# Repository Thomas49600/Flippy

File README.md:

# Flippy
Introducing Flippy! The all-in-one modular 3D printed electromechanical seven-segment display. Through the use of 14 electromagnets, each digit is able to quickly and mechanically display both numbers and letters. This creates a unique and satisfying display.

To build your own, check the full build instructions on Instructables: https://www.instructables.com/3D-Printed-Electromechanical-7-Segment-Display/

Or watch the YouTube video below (Link: https://youtu.be/np4NRMKOG6U)

This project falls under the CC BY-NC-SA 4.0 Licence

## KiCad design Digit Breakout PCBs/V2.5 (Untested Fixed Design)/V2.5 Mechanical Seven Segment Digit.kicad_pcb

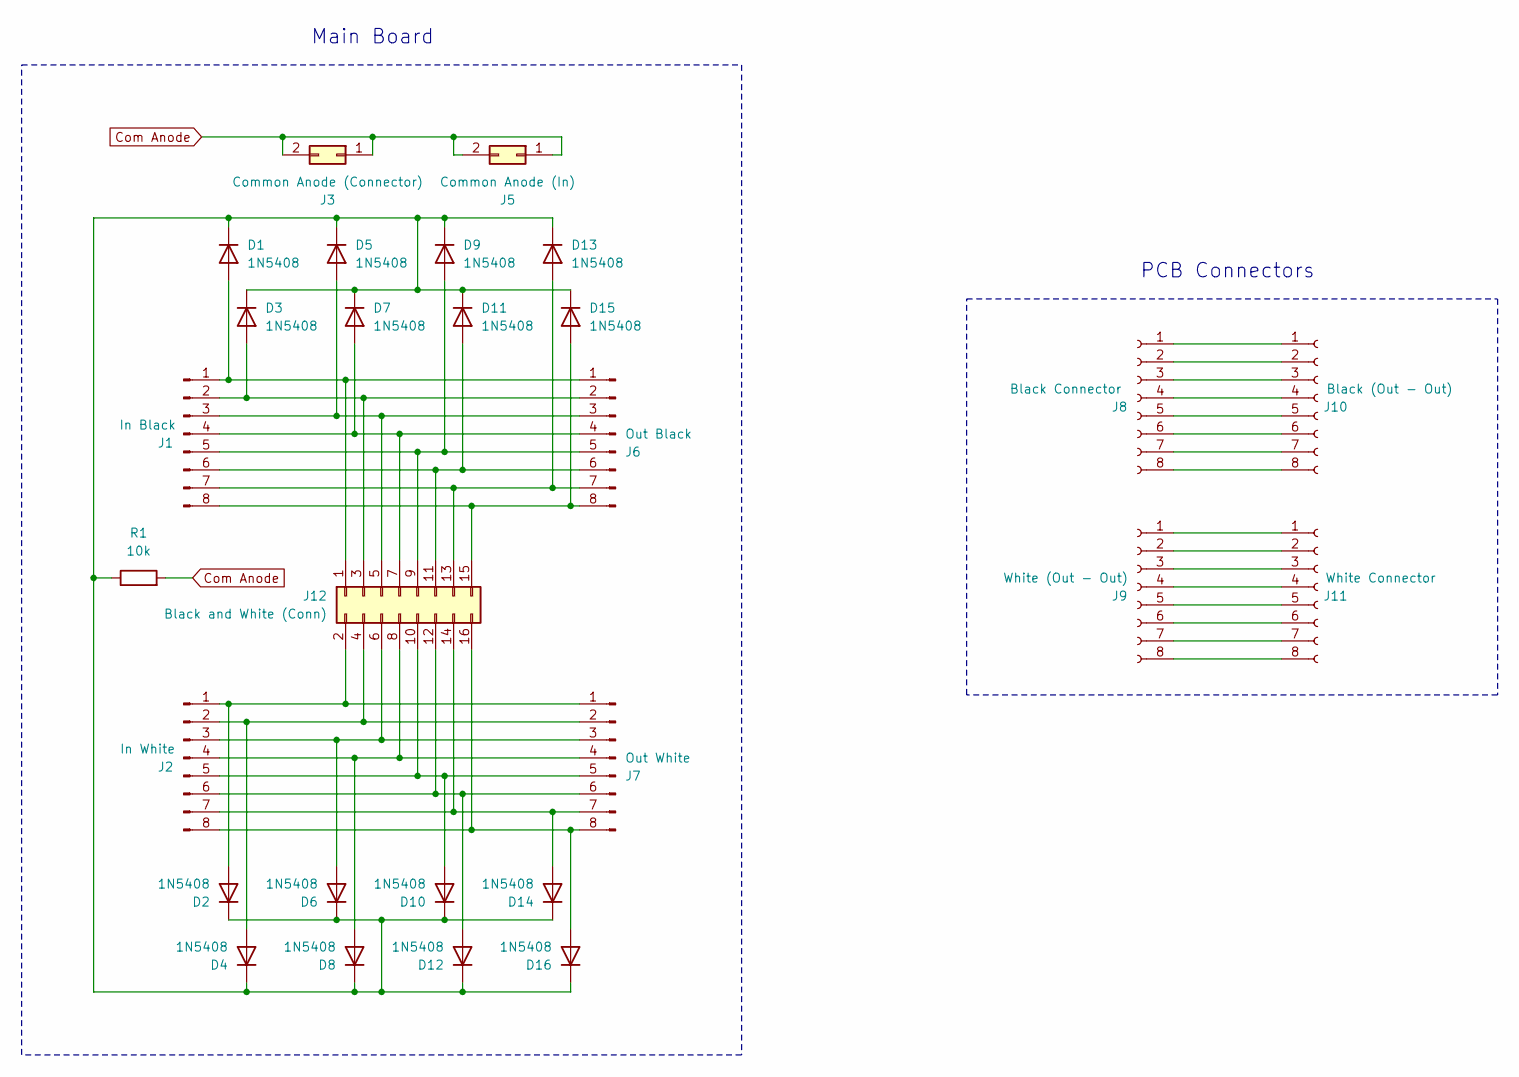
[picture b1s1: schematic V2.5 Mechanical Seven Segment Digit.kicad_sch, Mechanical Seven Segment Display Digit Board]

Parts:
D1, D2, D3, D4, D5, D6, D7, D8, D9, D10, D11, D12, D13, D14, D15, D16: 1N5408; D_DO-201AD_P15.24mm_Horizontal
J1: In Black; PinSocket_1x08_P2.54mm_Vertical
J2: In White; PinSocket_1x08_P2.54mm_Vertical
J3: Common Anode (Connector); PinSocket_2x01_P2.54mm_Vertical
J5: Common Anode (In); PinSocket_2x01_P2.54mm_Vertical
J6: Out Black; PinSocket_1x08_P2.54mm_Vertical
J7: Out White; PinSocket_1x08_P2.54mm_Vertical
J8: Black Connector; PinSocket_1x08_P2.54mm_Vertical
J9: White (Out - Out); PinSocket_1x08_P2.54mm_Vertical
J10: Black (Out - Out); PinSocket_1x08_P2.54mm_Vertical
J11: White Connector; PinSocket_1x08_P2.54mm_Vertical
J12: Black and White (Conn); PinSocket_2x08_P2.54mm_Vertical
R1: 10k; R_Axial_DIN0207_L6.3mm_D2.5mm_P7.62mm_Horizontal

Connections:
Com Anode: J3.1, J3.2, J5.1, J5.2, R1.2
unnamed: D1.2 (A), J1.1, J6.1, J12.1
unnamed: D1.1 (K), D2.1 (K), D3.1 (K), D4.1 (K), D5.1 (K), D6.1 (K), D7.1 (K), D8.1 (K), D9.1 (K), D10.1 (K), D11.1 (K), D12.1 (K), D13.1 (K), D14.1 (K), D15.1 (K), D16.1 (K), R1.1
unnamed: D2.2 (A), J2.1, J7.1, J12.2
unnamed: D3.2 (A), J1.2, J6.2, J12.3
unnamed: D4.2 (A), J2.2, J7.2, J12.4
unnamed: D5.2 (A), J1.3, J6.3, J12.5
unnamed: D6.2 (A), J2.3, J7.3, J12.6
unnamed: D7.2 (A), J1.4, J6.4, J12.7
unnamed: D8.2 (A), J2.4, J7.4, J12.8
unnamed: D9.2 (A), J1.5, J6.5, J12.9
unnamed: D10.2 (A), J2.5, J7.5, J12.10
unnamed: D11.2 (A), J1.6, J6.6, J12.11
unnamed: D12.2 (A), J2.6, J7.6, J12.12
unnamed: D13.2 (A), J1.7, J6.7, J12.13
unnamed: D14.2 (A), J2.7, J7.7, J12.14
unnamed: D15.2 (A), J1.8, J6.8, J12.15
unnamed: D16.2 (A), J2.8, J7.8, J12.16
unnamed: J8.1, J10.1
unnamed: J8.2, J10.2
unnamed: J8.3, J10.3
unnamed: J8.4, J10.4
unnamed: J8.5, J10.5
unnamed: J8.6, J10.6
unnamed: J8.7, J10.7
unnamed: J8.8, J10.8
unnamed: J9.1, J11.1
unnamed: J9.2, J11.2
unnamed: J9.3, J11.3
unnamed: J9.4, J11.4
unnamed: J9.5, J11.5
unnamed: J9.6, J11.6
unnamed: J9.7, J11.7
unnamed: J9.8, J11.8

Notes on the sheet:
Main Board
PCB Connectors

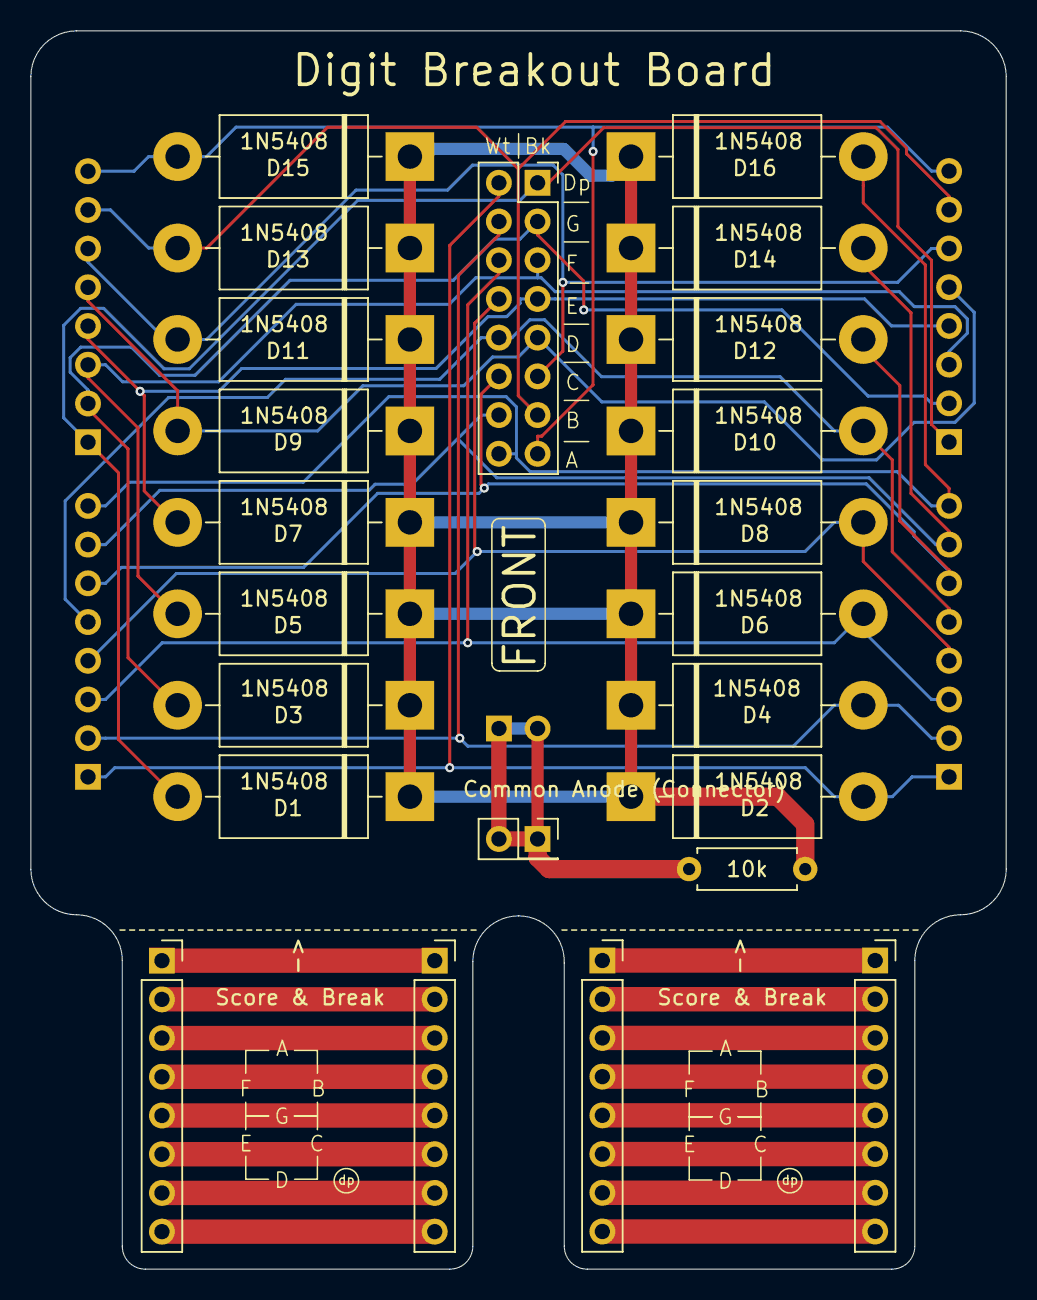
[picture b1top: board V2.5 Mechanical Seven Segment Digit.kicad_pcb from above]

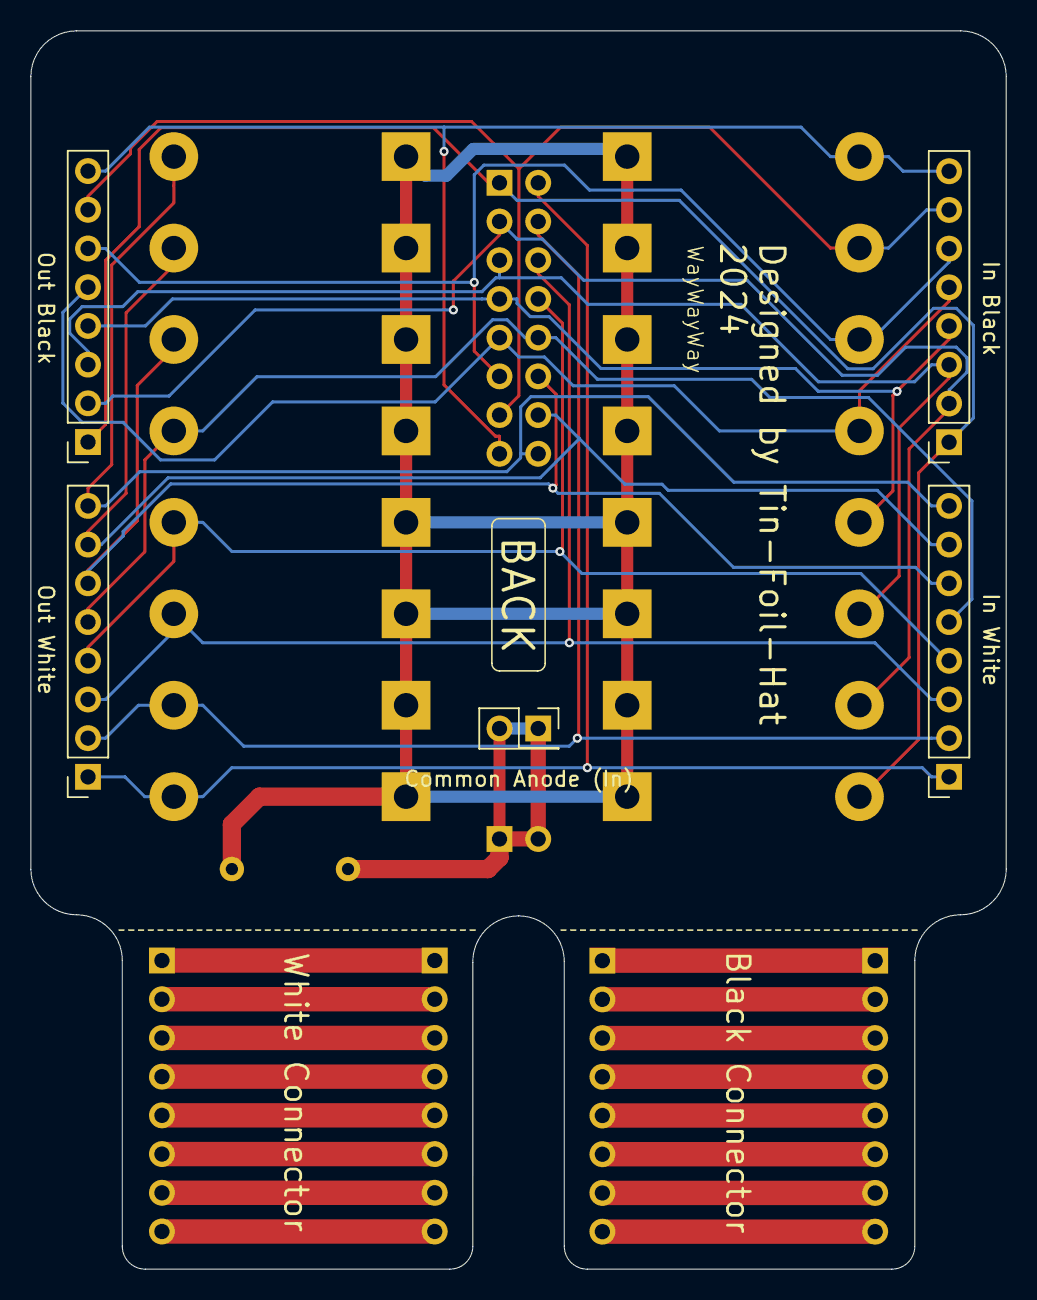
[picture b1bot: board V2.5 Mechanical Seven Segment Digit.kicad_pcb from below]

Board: 2 copper layers, 64.0 x 81.3 mm, 28 parts (5 on the bottom side), 34 nets.

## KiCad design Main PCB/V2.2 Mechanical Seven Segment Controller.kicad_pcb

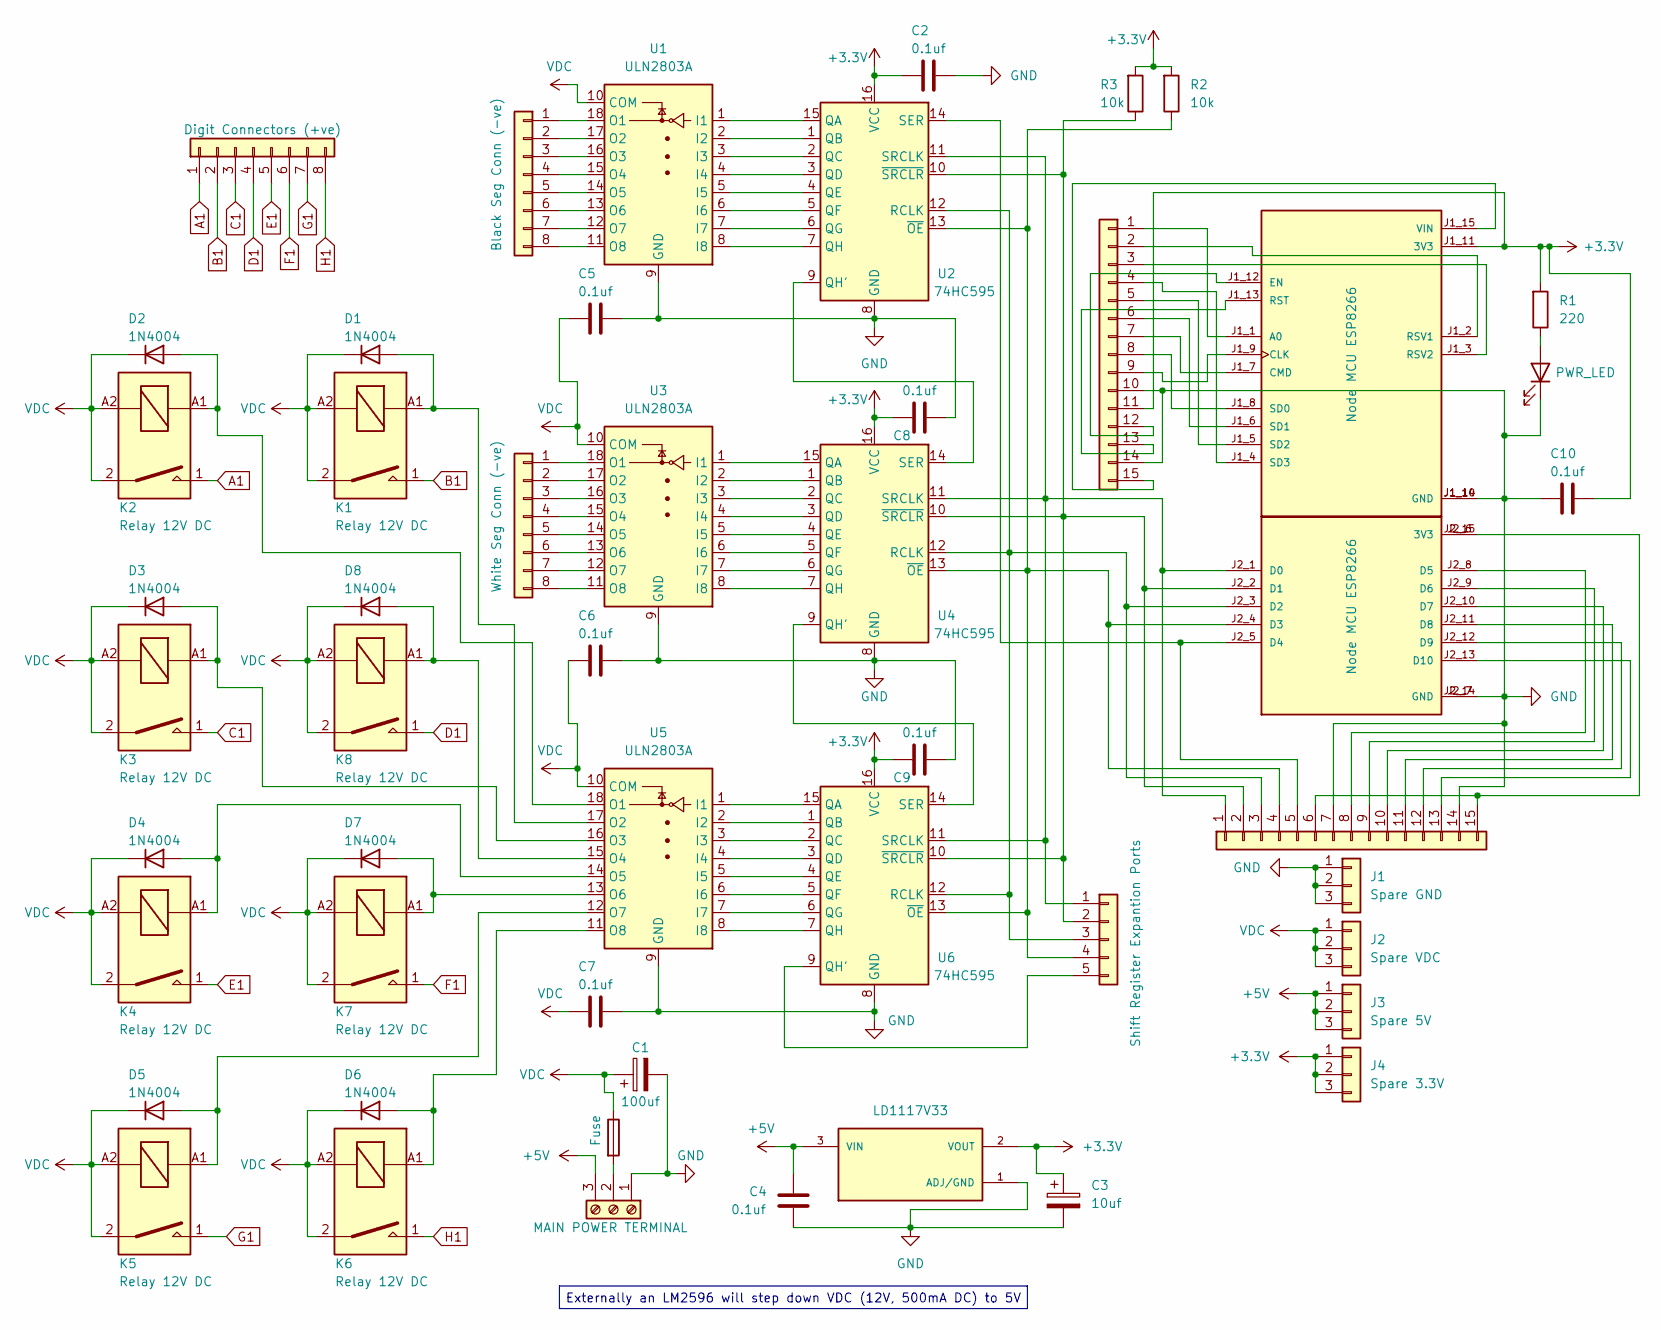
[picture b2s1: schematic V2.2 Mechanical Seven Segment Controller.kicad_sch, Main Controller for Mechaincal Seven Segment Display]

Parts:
A1: Node MCU ESP8266; SEEED_113990105; PARTREV N/A
C1: 100uf; CP_Radial_D10.0mm_P5.00mm
C2, C4, C5, C6, C7, C8, C9, C10: 0.1uf; C_Disc_D4.3mm_W1.9mm_P5.00mm
C3: 10uf; CP_Radial_D5.0mm_P2.00mm
D1, D2, D3, D4, D5, D6, D7, D8: 1N4004; D_DO-41_SOD81_P10.16mm_Horizontal
D9: PWR_LED; LED_D5.0mm
F1: Fuse; PinHeader_1x02_P2.54mm_Vertical
J1: Spare GND; PinHeader_1x03_P2.54mm_Vertical
J2: Spare VDC; PinHeader_1x03_P2.54mm_Vertical
J3: Spare 5V; PinHeader_1x03_P2.54mm_Vertical
J4: Spare 3.3V; PinHeader_1x03_P2.54mm_Vertical
J5: Black Seg Conn (-ve); PinHeader_1x08_P2.54mm_Vertical
J6, J9: ESP8266 Extra Pins; PinHeader_1x15_P2.54mm_Vertical
J7: White Seg Conn (-ve); PinHeader_1x08_P2.54mm_Vertical
J8: Digit Connectors (+ve); PinHeader_1x08_P2.54mm_Vertical
J10: Shift Register Expantion Ports; PinHeader_1x05_P2.54mm_Vertical
J11: MAIN POWER TERMINAL; 3_Way_Screw_Terminal_Altronics_(P2033B)
K1, K2, K3, K4, K5, K6, K7, K8: Relay 12V DC; Relay_SPST_Altronics_S4252B
R1: 220; R_Axial_DIN0207_L6.3mm_D2.5mm_P7.62mm_Horizontal
R2, R3: 10k; R_Axial_DIN0207_L6.3mm_D2.5mm_P7.62mm_Horizontal
U1, U3, U5: ULN2803A; 18_Pin_DIL_IC_Socket
U2, U4, U6: 74HC595; 16_Pin_DIL_IC_Socket
U7: LD1117V33; TO255P1020X450X1968-3; PARTREV 37

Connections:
+3.3V: A1.J1_11 (3V3), C2.2, C3.1, C8.2, C9.2, C10.1, J4.1, J4.2, J4.3, J6.11, R1.2, R2.2, R3.2, U2.16 (VCC), U4.16 (VCC), U6.16 (VCC), U7.2 (VOUT)
+5V: C4.1, J3.1, J3.2, J3.3, J11.3, U7.3 (VIN)
A1: J8.1, K2.1
B1: J8.2, K1.1
C1: J8.3, K3.1
D1: J8.4, K8.1
E1: J8.5, K4.1
F1: J8.6, K7.1
G1: J8.7, K5.1
GND: A1.J1_10 (GND), A1.J1_14 (GND), A1.J2_7 (GND), A1.J2_14 (GND), C1.2, C2.1, C3.2, C4.2, C5.1, C6.1, C7.1, C8.1, C9.1, C10.2, D9.1 (K), J1.1, J1.2, J1.3, J6.10, J6.14, J9.7, J9.14, J11.1, U1.9 (GND), U2.8 (GND), U3.9 (GND), U4.8 (GND), U5.9 (GND), U6.8 (GND), U7.1 (ADJ/GND)
H1: J8.8, K6.1
unnamed: A1.J1_1 (A0), J6.1
unnamed: A1.J1_9 (CLK), J6.9
unnamed: A1.J1_7 (CMD), J6.7
unnamed: A1.J1_12 (EN), J6.12
unnamed: A1.J1_13 (RST), J6.13
unnamed: A1.J1_2 (RSV1), J6.2
unnamed: A1.J1_3 (RSV2), J6.3
unnamed: A1.J1_8 (SD0), J6.8
unnamed: A1.J1_6 (SD1), J6.6
unnamed: A1.J1_5 (SD2), J6.5
unnamed: A1.J1_4 (SD3), J6.4
unnamed: A1.J1_15 (VIN), J6.15
unnamed: A1.J2_1 (D0), J9.1, J10.1, U2.11 (SRCLK), U4.11 (SRCLK), U6.11 (SRCLK)
unnamed: A1.J2_2 (D1), J9.2, J10.2, R3.1, U2.10 (~SRCLR), U4.10 (~SRCLR), U6.10 (~SRCLR)
unnamed: A1.J2_3 (D2), J9.3, J10.3, U2.12 (RCLK), U4.12 (RCLK), U6.12 (RCLK)
unnamed: A1.J2_4 (D3), J9.4, J10.4, R2.1, U2.13 (~OE), U4.13 (~OE), U6.13 (~OE)
unnamed: A1.J2_5 (D4), J9.5, U2.14 (SER)
unnamed: A1.J2_8 (D5), J9.8
unnamed: A1.J2_9 (D6), J9.9
unnamed: A1.J2_10 (D7), J9.10
unnamed: A1.J2_11 (D8), J9.11
unnamed: A1.J2_12 (D9), J9.12
unnamed: A1.J2_13 (D10), J9.13
unnamed: D1.2 (A), K1.A1, U5.17 (O2)
unnamed: D2.2 (A), K2.A1, U5.18 (O1)
unnamed: D3.2 (A), K3.A1, U5.16 (O3)
unnamed: D4.2 (A), K4.A1, U5.14 (O5)
unnamed: D5.2 (A), K5.A1, U5.12 (O7)
unnamed: D6.2 (A), K6.A1, U5.11 (O8)
unnamed: D7.2 (A), K7.A1, U5.13 (O6)
unnamed: D8.2 (A), K8.A1, U5.15 (O4)
unnamed: D9.2 (A), R1.1
unnamed: J5.1, U1.18 (O1)
unnamed: J5.2, U1.17 (O2)
unnamed: J5.3, U1.16 (O3)
unnamed: J5.4, U1.15 (O4)
unnamed: J5.5, U1.14 (O5)
unnamed: J5.6, U1.13 (O6)
unnamed: J5.7, U1.12 (O7)
unnamed: J5.8, U1.11 (O8)
unnamed: J7.1, U3.18 (O1)
unnamed: J7.2, U3.17 (O2)
unnamed: J7.3, U3.16 (O3)
unnamed: J7.4, U3.15 (O4)
unnamed: J7.5, U3.14 (O5)
unnamed: J7.6, U3.13 (O6)
unnamed: J7.7, U3.12 (O7)
unnamed: J7.8, U3.11 (O8)
unnamed: A1.J2_6 (3V3), A1.J2_15 (3V3), J9.6, J9.15
unnamed: J10.5, U6.9 (QH')
unnamed: F1.2, J11.2
unnamed: U1.1 (I1), U2.15 (QA)
unnamed: U1.2 (I2), U2.1 (QB)
unnamed: U1.3 (I3), U2.2 (QC)
unnamed: U1.4 (I4), U2.3 (QD)
unnamed: U1.5 (I5), U2.4 (QE)
unnamed: U1.6 (I6), U2.5 (QF)
unnamed: U1.7 (I7), U2.6 (QG)
unnamed: U1.8 (I8), U2.7 (QH)
unnamed: U2.9 (QH'), U4.14 (SER)
unnamed: U3.1 (I1), U4.15 (QA)
unnamed: U3.2 (I2), U4.1 (QB)
unnamed: U3.3 (I3), U4.2 (QC)
unnamed: U3.4 (I4), U4.3 (QD)
unnamed: U3.5 (I5), U4.4 (QE)
unnamed: U3.6 (I6), U4.5 (QF)
unnamed: U3.7 (I7), U4.6 (QG)
unnamed: U3.8 (I8), U4.7 (QH)
unnamed: U4.9 (QH'), U6.14 (SER)
unnamed: U5.1 (I1), U6.15 (QA)
unnamed: U5.2 (I2), U6.1 (QB)
unnamed: U5.3 (I3), U6.2 (QC)
unnamed: U5.4 (I4), U6.3 (QD)
unnamed: U5.5 (I5), U6.4 (QE)
unnamed: U5.6 (I6), U6.5 (QF)
unnamed: U5.7 (I7), U6.6 (QG)
unnamed: U5.8 (I8), U6.7 (QH)
VDC: C1.1, C5.2, C6.2, C7.2, D1.1 (K), D2.1 (K), D3.1 (K), D4.1 (K), D5.1 (K), D6.1 (K), D7.1 (K), D8.1 (K), F1.1, J2.1, J2.2, J2.3, K1.2, K1.A2, K2.2, K2.A2, K3.2, K3.A2, K4.2, K4.A2, K5.2, K5.A2, K6.2, K6.A2, K7.2, K7.A2, K8.2, K8.A2, U1.10 (COM), U3.10 (COM), U5.10 (COM)

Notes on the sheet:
Externally an LM2596 will step down VDC (12V, 500mA DC) to 5V

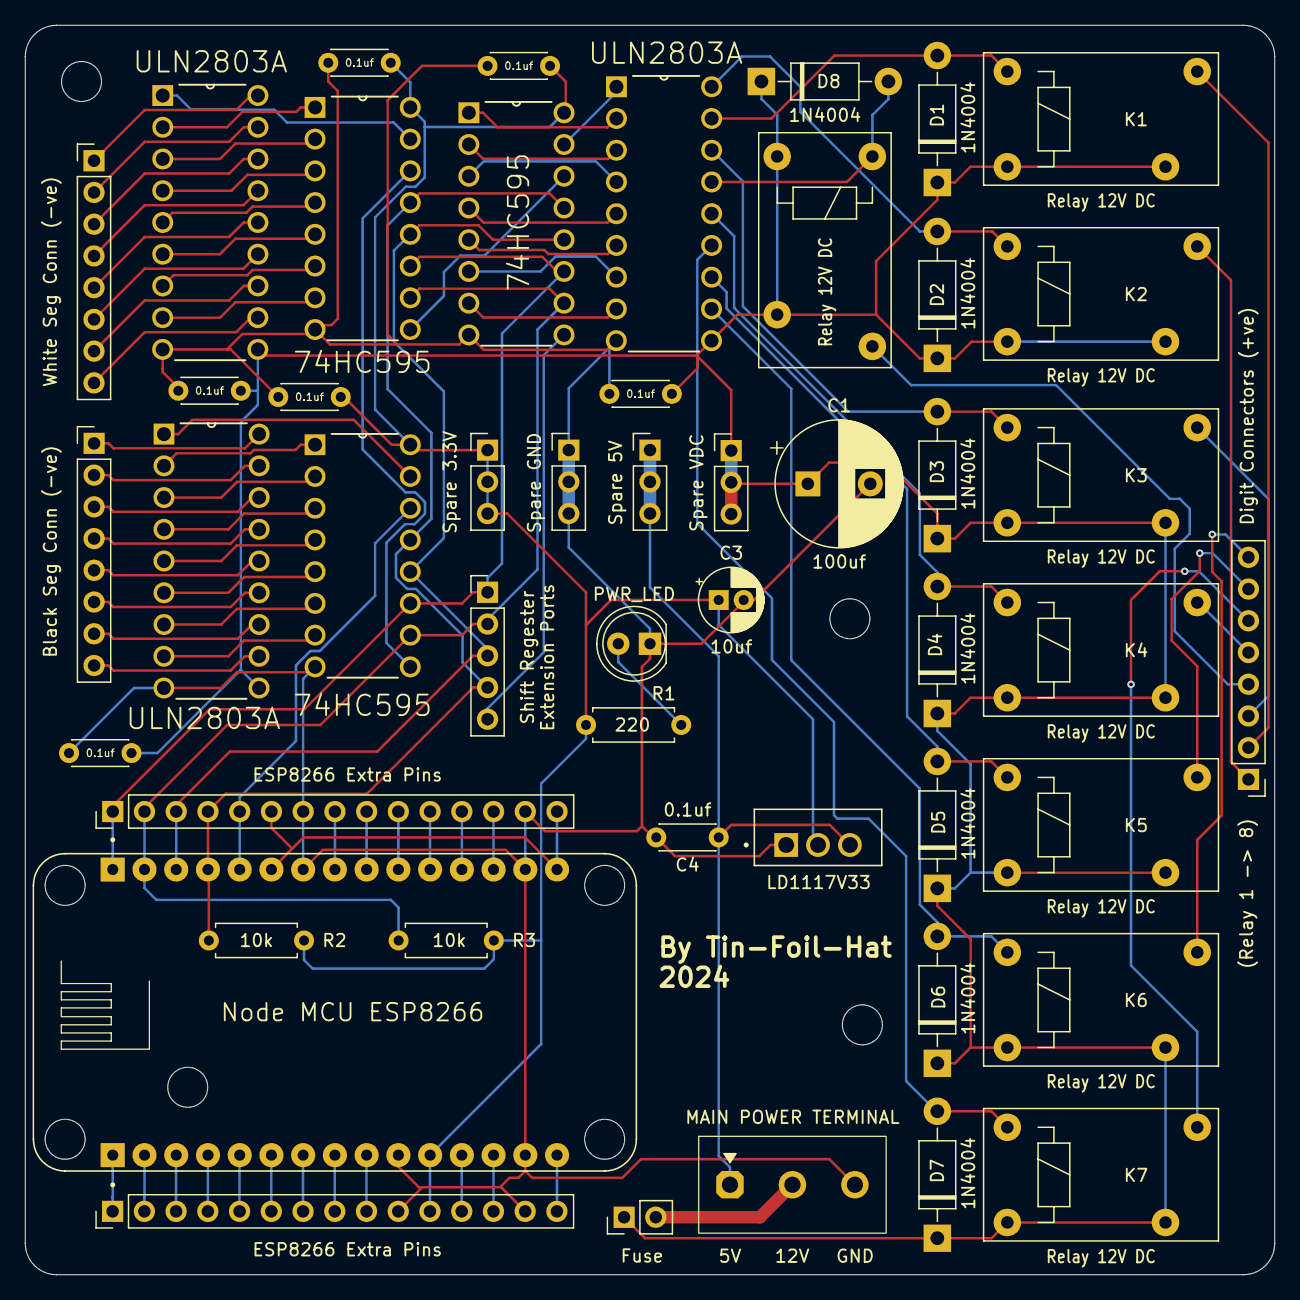
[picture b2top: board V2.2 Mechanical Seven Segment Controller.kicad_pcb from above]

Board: 2 copper layers, 100.0 x 100.0 mm, 49 parts (0 on the bottom side), 89 nets.
